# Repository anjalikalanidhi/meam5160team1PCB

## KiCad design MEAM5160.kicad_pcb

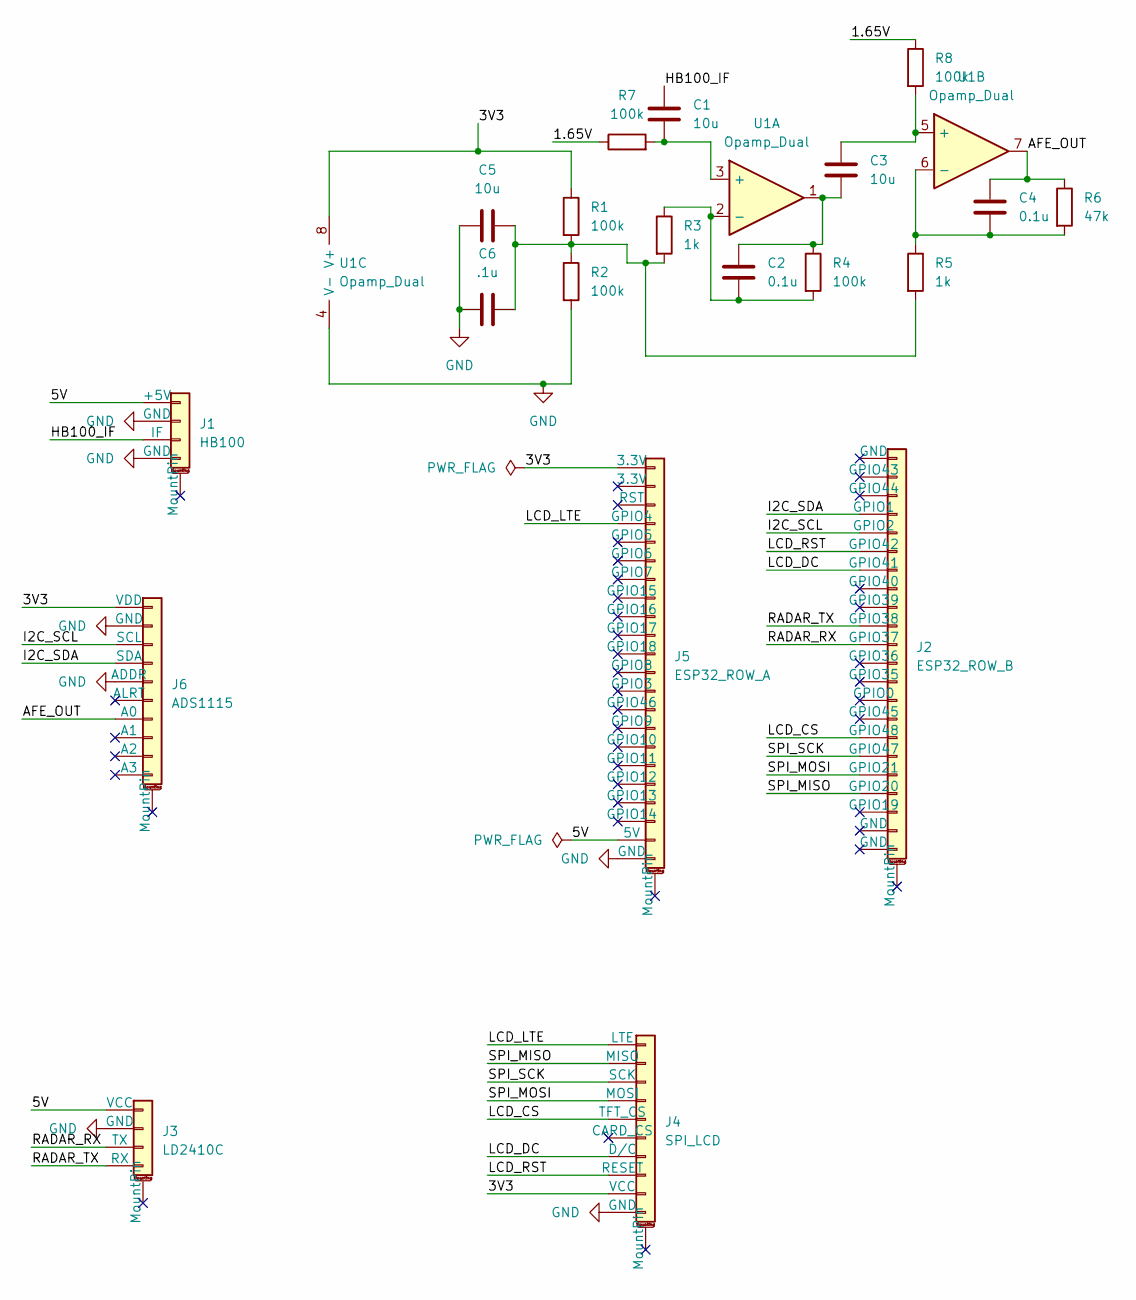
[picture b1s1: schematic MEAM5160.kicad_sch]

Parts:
C1, C5: 10u; C_0805_2012Metric
C2, C4: 0.1u; C_0805_2012Metric
C3: 10u; C_1206_3216Metric
C6: .1u; C_0805_2012Metric
J1: HB100; PinHeader_1x04_P2.54mm_Vertical
J2: ESP32_ROW_B; PinSocket_1x22_P2.54mm_Vertical
J3: LD2410C; PinHeader_1x04_P2.54mm_Vertical
J4: SPI_LCD; PinHeader_1x10_P2.54mm_Vertical
J5: ESP32_ROW_A; PinSocket_1x22_P2.54mm_Vertical
J6: ADS1115; PinHeader_1x10_P2.54mm_Vertical
R1, R2, R4, R7, R8: 100k; R_0805_2012Metric
R3, R5: 1k; R_0805_2012Metric
R6: 47k; R_0805_2012Metric
U1: Opamp_Dual; DIP-8_W7.62mm

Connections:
/1.65V: R7.1, R8.1
/3V3: J4.9 (VCC), J5.1 (3.3V), J6.1 (VDD), R1.1, U1.8 (V+)
/5V: J1.1 (+5V), J3.1 (VCC), J5.21 (5V)
/AFE_OUT: C4.1, J6.7 (A0), R6.1, U1.7
/HB100_IF: C1.1, J1.3 (IF)
/I2C_SCL: J2.5 (GPIO2), J6.3 (SCL)
/I2C_SDA: J2.4 (GPIO1), J6.4 (SDA)
/LCD_CS: J2.16 (GPIO48), J4.5 (TFT_CS)
/LCD_DC: J2.7 (GPIO41), J4.7 (D/C)
/LCD_LTE: J4.1 (LTE), J5.4 (GPIO4)
/LCD_RST: J2.6 (GPIO42), J4.8 (RESET)
/RADAR_RX: J2.11 (GPIO37), J3.3 (TX)
/RADAR_TX: J2.10 (GPIO38), J3.4 (RX)
/SPI_MISO: J2.19 (GPIO20), J4.2 (MISO)
/SPI_MOSI: J2.18 (GPIO21), J4.4 (MOSI)
/SPI_SCK: J2.17 (GPIO47), J4.3 (SCK)
GND: C5.1, C6.1, J1.2 (GND), J1.4 (GND), J3.2 (GND), J4.10 (GND), J5.22 (GND), J6.2 (GND), J6.5 (ADDR), R2.2, U1.4 (V-)
unnamed: C2.1, C3.2, R4.1, U1.1
unnamed: C5.2, C6.2, R1.2, R2.1, R3.2, R5.2
unnamed: C1.2, R7.2, U1.3 (+)
unnamed: C2.2, R3.1, R4.2, U1.2 (-)
unnamed: C3.1, R8.2, U1.5 (+)
unnamed: C4.2, R5.1, R6.2, U1.6 (-)

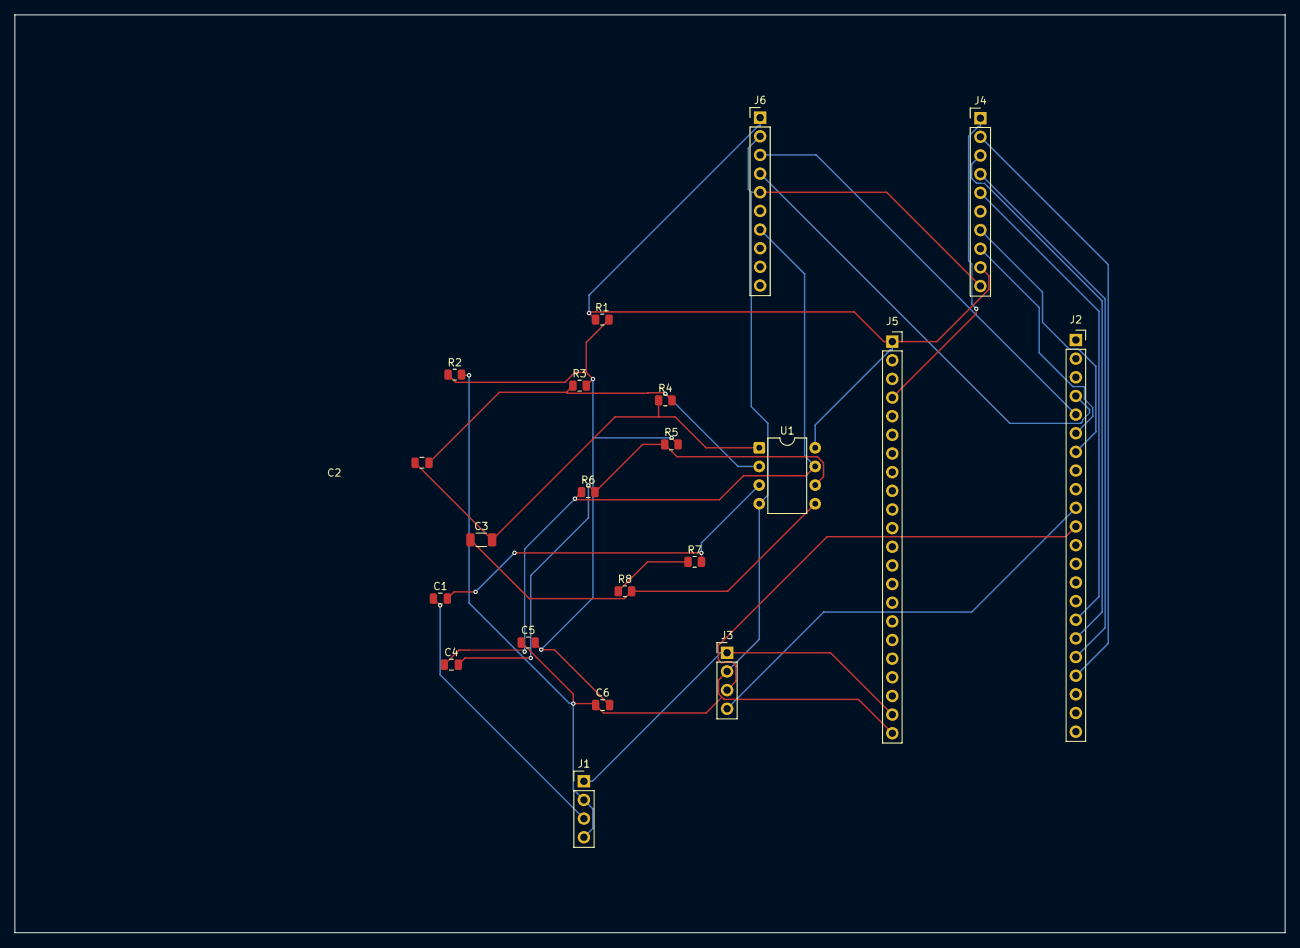
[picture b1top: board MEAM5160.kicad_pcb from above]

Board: 2 copper layers, 173.0 x 125.0 mm, 21 parts (0 on the bottom side), 23 nets.
